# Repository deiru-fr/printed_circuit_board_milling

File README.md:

# PCB-milling

PCB milling can be seen as printing a circuit on to a piece of copper. This allows us to
check our design before having it Professionally made.

The milling is done on a copper substrate, it is a piece of fiber glass which has one side or both side 
covered in copper. The copper layers are what form the traces after being put through the milling machine.

The main purpuse here is to test different end mills and settings to get a decent result in PCB milling

## CNC Router

A CNC router is a computer-controlled cutting machine related to the hand held router used for cutting various 
hard materials, such as wood, composites, aluminium, steel, plastics, and foams. CNC stands for computer numerical control.
Here the following CNC router is tested for the PCB milling process.

This CNC router is from [CNC Shop](http://www.cnc-shop.ch/cnc3040.html)

* Model: 3040 v3.0
* Weight: 40kg
* Materiel: Casted aluminium
* Spindle speed: 6000 - 24000 tr/min
* Spindle power: 800W
* Collet fixture: ER11

Dimensions |  X  |  Y  |  Z  |
-----------|-----|-----|-----|
Travel size| 300 | 400 |  50
Table siez | 320 | 580 |  85

## Milling bits

Milling cutters are cutting tools typically used in milling machines or machining centers to perform milling operations They remove material by their movement within the machine or directly from the cutter's shape. The milling bits are fixed to the spindle by usinf ER 11 collet.
Tool Shank Diameter : 3 mm

### Trace cutout bits (Endmill)

Precision endmills are used to cut out the copper so that traces
are formed on the copper conductor.

* Solid Carbide V-Shaped Engraving Tool Bit

Included angle | Tip width | Price | Suplier
---------------|:----------|:------|:-----
       10°     |    0.1    | 5 bits for 6,50 € |[Amazon](https://www.amazon.fr/gp/product/B00D3GU558/ref=oh_aui_detailpage_o03_s00?ie=UTF8&psc=1) |
       15°     |    0.1    | 1 bit for 13,50 € |[Iron wood](http://www.ironwood-distribution.com/stylets_diametre_3/stylet_d3_angle_15%C2%B0/stylet-ve-diametre-a15-e0-10-p-3842.html) |
       45°     |    0.1    | 10 bits for 1 € |[Ebay](https://www.ebay.com/itm/1-5-10PCS-Carbure-Gravure-CNC-PCB-45-0-1mm-Fraise-Foret-Couteau-Plat-3-17MM/322578275122?ssPageName=STRK%3AMEBIDX%3AIT&var=511564367365&_trksid=p2057872.m2749.l2649) |
       10°     |    0.2    | 1 bit for 4.99 € |[Ebay](https://www.ebay.com/itm/%C3%98-3x10-X-0-2mm-type-V-Burins-de-GRAVURE-pour-cnc-machine-Graveur/391434920942?ssPageName=STRK%3AMEBIDX%3AIT&_trksid=p2057872.m2749.l2649) |
       15°     |    0.2    | 1 bit for 13,50 € |[Iron wood](http://www.ironwood-distribution.com/stylets_diametre_3/stylet_d3_angle_15%C2%B0/stylet-ve-diametre-a15-e0-10-p-3842.html) |

* Tough Tip Engraving Tool

Flute | Included angle | Tip width | Price | Suplier
:-----|:---------------|:----------|:------|:-----
 1    |       25°      |    0.2    | 1 bit for 9,60 € |[CNC Fraises](https://www.cncfraises.fr/pointes-javelots-1-dent-evo/237-pointe-javelot-1-dent-25-degres-gravure-circuit-imprime.html) |

* Other interesting engraving tips

http://www.2linc.com/engraving_tools_tough_tip.htm
http://www.2linc.com/engraving_tools_composite.htm

### Drill bits

Used to drill holes for through hole parts and mouting holes.

* Micro drill bits

D      | L1     | A     |  Price | Suplier
-------|:-------|:------|:-------|:--------
0.6 mm |7.0 mm  |  130° |3,40 €  |[Iron wood](http://www.ironwood-distribution.com/outils_fraisage/micros_forets/micro-foret-60-17-hss-p-3165.html) |
0.7 mm |10.5 mm |  130° |3,40 €  |[Iron wood](http://www.ironwood-distribution.com/outils_fraisage/micros_forets/micro-foret-70-17-hss-p-3167.html)
0.8 mm |10.5 mm |  130° |3,40 €  |[Iron wood](http://www.ironwood-distribution.com/outils_fraisage/micros_forets/micro-foret-80-17-hss-p-3169.html)
1.0 mm |10.5 mm |  130° |3,40 €  |[Iron wood](http://www.ironwood-distribution.com/outils_fraisage/micros_forets/micro-foret-17-hss-p-3173.html)
1.2 mm |10.5 mm |  130° |3,40 €  |[Iron wood](http://www.ironwood-distribution.com/outils_fraisage/micros_forets/micro-foret-20-17-hss-p-3177.html)
1.5 mm |10.5 mm |  130° |3 €     |[Iron wood](http://www.ironwood-distribution.com/outils_fraisage/micros_forets/micro-foret-50-17-hss-p-3181.html)
3.0 mm |10.5 mm |  130° |3 €     |[Iron wood](http://www.ironwood-distribution.com/outils_fraisage/micros_forets/micro-foret-00-17-hss-p-3196.html)

### Routing cut-out bit

Used to cut out pcb once milling is finished

* Titanium Coat Carbide

D                |  Price | Suplier
-----------------|:-------|:-----------
0.6 mm to 1,5 mm |3,40 €  |[Amazon](https://www.amazon.fr/gp/product/B00OPY6R6I/ref=oh_aui_detailpage_o02_s00?ie=UTF8&psc=1) |

## Softwares

* CNC : Mach3
* Eagle CAD
* [pcb-gcode](http://pcbgcode.org/list.php?12)

## Tutorials

* [sparkfun](https://learn.sparkfun.com/tutorials/using-eagle-schematic)
* [Instructable](http://www.instructables.com/id/Make-your-own-PCBs-on-an-inexpensive-desktop-CNC-m/)

## Supplier

* [Ironwood](http://www.ironwood-distribution.com/outils_fraisage-c-20.html)
* [CNC Frainses](https://www.cncfraises.fr/)
* [2linc](http://www.2linc.com/)

## What Not To Do
* Don't drop the bits. They will break.
* Don't crash the tool. You'll feel bad when you crash the tool and probably won't do it again. Just raise the spindle before you go crazy hitting return to zero and if you stop a program don't just restart it somewhere in the middle and expect everything to be OK.
* Don't forget to wear eye protection. The CNC machine is a robot that cuts things and it's not sophisticated enough to follow Asimov's laws about not hurling bits of metal into your eye.
* Don't start and stop the PC with the spindle turned on. That thing is just hooked up to a pin on the parallel port and that pin gets mercilessly diddled by legacy windows upnp probing which may surprise and/or hurt you by running the spindle. Just turn it off.
* Don't leave the mill running unattended. You need to be there to hit the pretty red e-stop button when something horrible happens.
* Don't leave a mess for the next person.

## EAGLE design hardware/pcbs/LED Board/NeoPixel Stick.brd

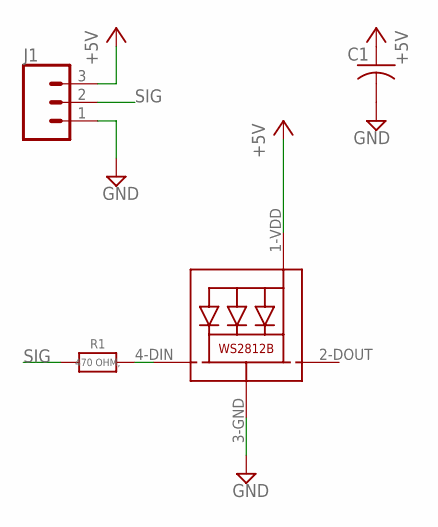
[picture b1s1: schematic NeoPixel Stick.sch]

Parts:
C1: C-USC0805K; C0805K
J1: CONN_03LONGPADS; 1X03_LONGPADS
LED1: WS2812B5050; WS2812B
R1: 470 OHM,; _0805MP

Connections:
+5V: C1.1, J1.3, LED1.1-VDD (VDD)
GND: C1.2, J1.1, LED1.3-GND (GND)
unnamed: LED1.4-DIN (DI), R1.2
SIG: J1.2, R1.1

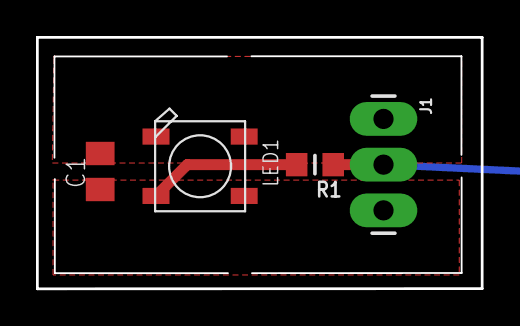
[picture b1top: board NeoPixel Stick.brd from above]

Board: 2 copper layers, 24.7 x 14.0 mm, 4 parts (0 on the bottom side), 4 nets.

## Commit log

2018-08-07 read me

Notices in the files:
parts and their libraries:
microbuilder: This work is placed in the public domain, and may be freely used for commercial and non-commercial work with the following conditions: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
SparkFun-Connectors: Licensing: Creative Commons ShareAlike 4.0 International - https://creativecommons.org/licenses/by-sa/4.0
